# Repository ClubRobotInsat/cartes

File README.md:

# Cartes du club robot

Toutes les cartes ici sont les cartes en développement au club. Vous pouvez retrouver
dans les release les cartes correspondant à chaque robot.

Dans le dossier `manufactured` vous pouvez retrouver toutes les cartes qui ont été fabriquées. Elles sont
identifiées par un code unique que vous pouvez retrouver sur le PCB.

## Procédure de fabrication

Lorsque vous envoyez une carte à fabriquer, il faut:
- Ajouter un identifiant à la carte (de la forme `[A-Z]{3}`)
- Copier le projet dans le dossier `manufactured`
- Renommer le projet en `[identifiant] {nom}`

Cela permet d'avoir une trace exacte de toutes les cartes fabriquées. Une carte dans le dossier `manufactured` n'est pas
forcément définitive, mais cela permet d'identifier les cartes que nous pouvons trouver dans le local.

## Procédure post-coupe

Lorsque la coupe est finie il faut produire une release contenant toutes les cartes utilisées, c'est pratique pour comprendre
comment fonctionnait le robot.

## Cartes

### Alimentation

Carte principale d'alimentation du robot, adapte la tension batterie pour alimenter les différets composants.

### Base roulante

Carte pour la gestion de la base roulante du robot

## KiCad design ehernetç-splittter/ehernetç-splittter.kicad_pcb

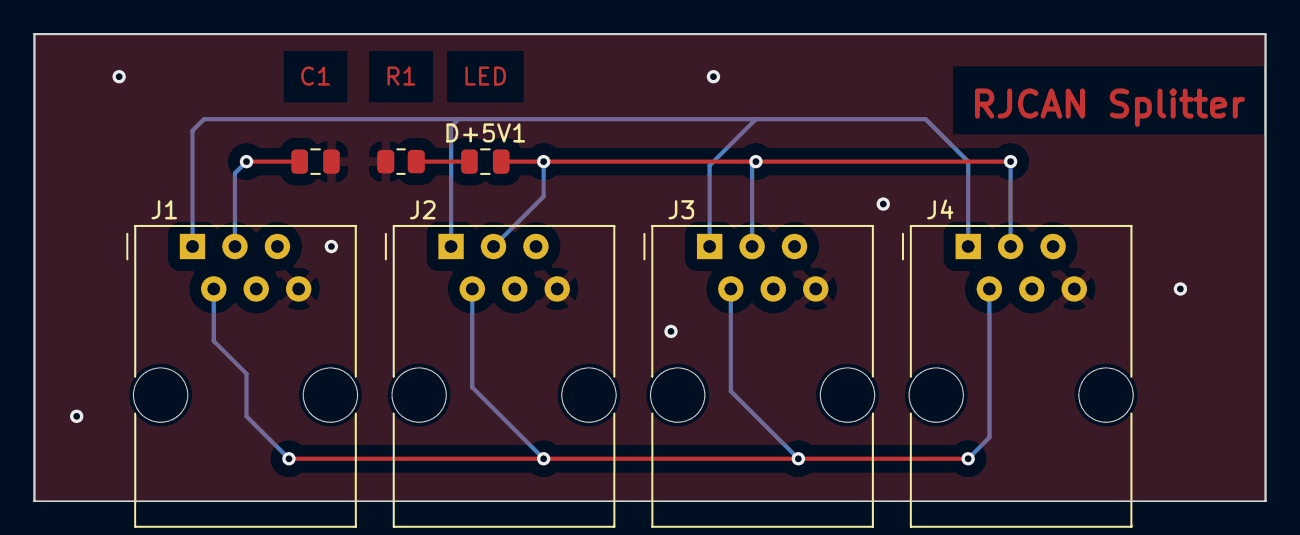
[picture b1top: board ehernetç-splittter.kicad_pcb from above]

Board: 2 copper layers, 73.7 x 27.9 mm, 7 parts (0 on the bottom side), 5 nets.

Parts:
C1: C_Polarized; C_0805_2012Metric
D+5V1: LED; C_0805_2012Metric
J1, J2, J3, J4: RJ_can; RJ12
R1: R; R_0805_2012Metric

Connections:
+5V: C1.1, D+5V1.2 (A), J1.3 (+5V), J2.3 (+5V), J3.3 (+5V), J4.3 (+5V)
CANH: J1.2 (CANH), J2.2 (CANH), J3.2 (CANH), J4.2 (CANH)
CANL: J1.1 (CANL), J2.1 (CANL), J3.1 (CANL), J4.1 (CANL)
GND: C1.2, J1.6 (GND), J2.6 (GND), J3.6 (GND), J4.6 (GND), R1.2
unnamed: D+5V1.1 (K), R1.1

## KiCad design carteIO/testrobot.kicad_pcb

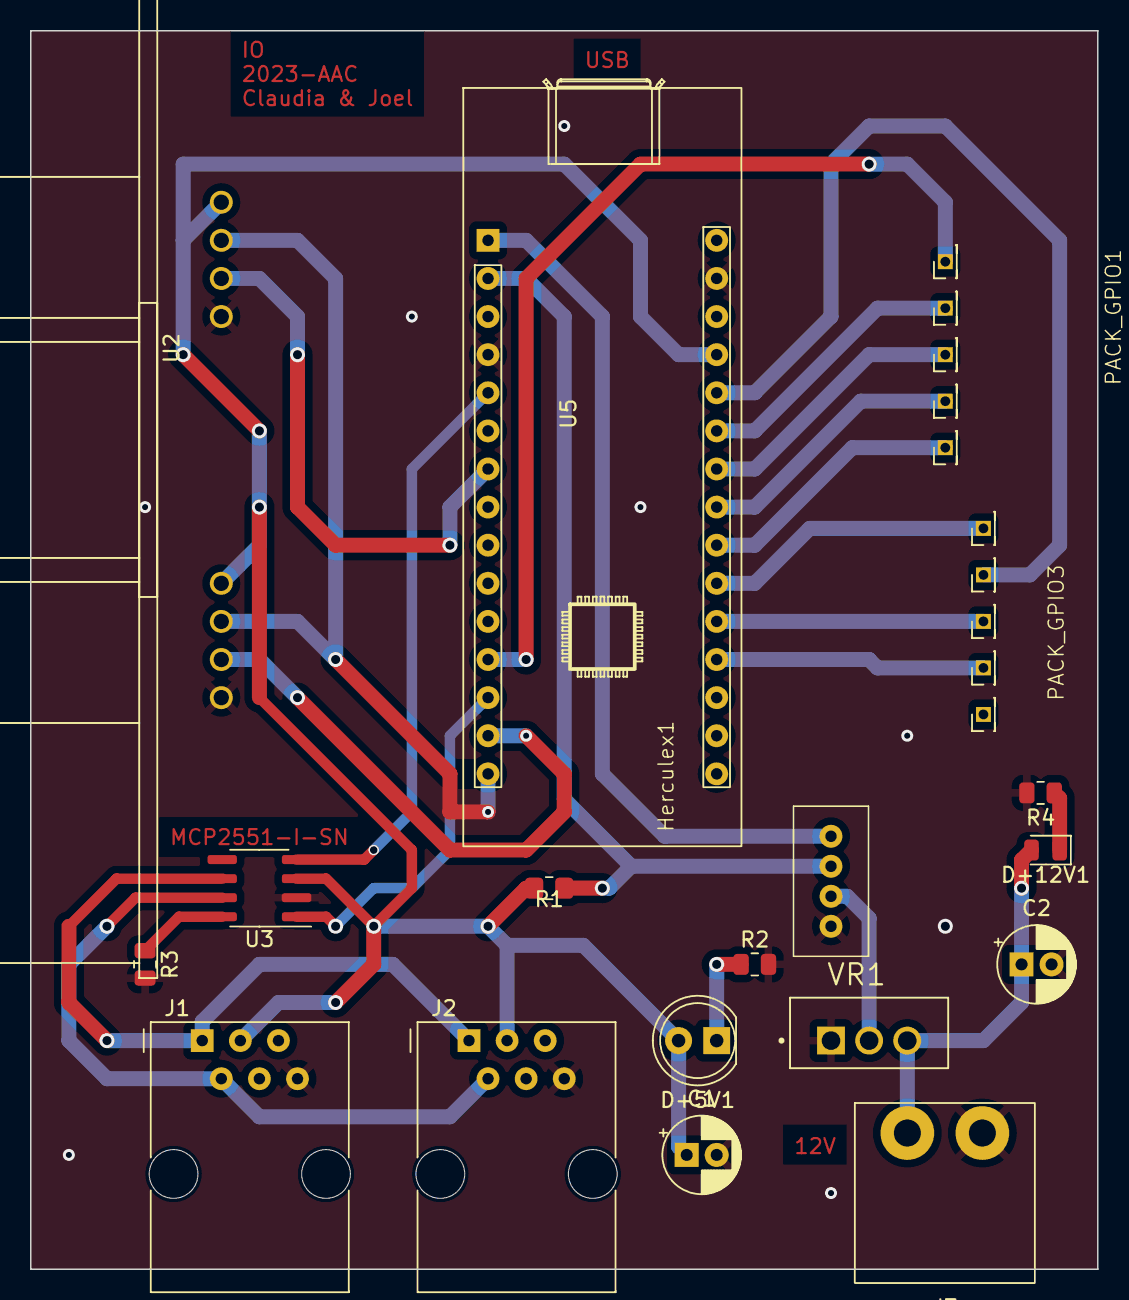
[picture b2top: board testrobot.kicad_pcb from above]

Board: 2 copper layers, 71.1 x 82.6 mm, 19 parts (0 on the bottom side), 26 nets.

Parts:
C1: C_Polarized; CP_Radial_D5.0mm_P2.00mm
C2: 470u; CP_Radial_D5.0mm_P2.00mm
D+5V1: LED; LED_D5.0mm
D+12V1: LED bleu; LED_0805_2012Metric
Herculex1: herculex
J1, J2: RJ_can; RJ12
J3: connector_power; WR_TBL_3137_2pins
PACK_GPIO1, PACK_GPIO3: gpio
R1: 4700; R_0805_2012Metric_Pad1.20x1.40mm_HandSolder
R2, R3: R; R_0805_2012Metric
R4: 1k; R_0805_2012Metric
U1, U2: HC-SR04; XCVR_HC-SR04
U3: MCP2551-I-SN; SOIC-8_3.9x4.9mm_P1.27mm
U5: Nucleo_STM32G431KB
VR1: LM317T/NOPB; TO254P1054X470X1955-3

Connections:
+5V: C1.1, D+5V1.2 (A), J1.3 (+5V), J2.3 (+5V), R1.1, U1.1 (VCC), U2.1 (VCC), U3.3 (VDD), U5.27 (+5V)
+8V: Herculex1.2 (+8V), VR1.2 (VOUT)
+12V: C2.1, D+12V1.2 (A), J3.1 (+12V), VR1.3 (VIN)
CANH: J1.2 (CANH), J2.2 (CANH), U3.7 (CANH)
CANL: J1.1 (CANL), J2.1 (CANL), U3.6 (CANL)
CAN_RX: U3.4 (RXD), U5.5 (PA12)
CAN_TX: U3.1 (TXD), U5.13 (PA11)
Echo_b5: U2.3 (ECHO), U5.14 (PB5)
Echo_b7: U1.3 (ECHO), U5.7 (PB7)
GND: C1.2, C2.2, Herculex1.1 (GND), J1.6 (GND), J2.6 (GND), J3.2 (GND), R2.2, R3.2, R4.2, U1.4 (GND), U2.4 (GND), U3.2 (VSS), U5.4 (GND), U5.29 (GND), VR1.1 (ADJ)
unnamed: D+5V1.1 (K), R2.1
unnamed: D+12V1.1 (K), R4.1
unnamed: R3.1, U3.8 (Rs)
unnamed: U5.3 (~RST), U5.28 (~RST)
PA0: PACK_GPIO3.2 (GPIO2), U5.19 (PA0)
PA1: PACK_GPIO3.3 (GPIO3), U5.20 (PA1)
PA2: PACK_GPIO3.4 (GPIO4), U5.26 (PA2)
PA3: PACK_GPIO3.5 (GPIO5), U5.21 (PA3)
PA4: PACK_GPIO1.1 (GPIO1), U5.22 (PA4)
PA5: PACK_GPIO1.2 (GPIO2), U5.23 (PA5/PB7)
PA6: PACK_GPIO1.3 (GPIO3), U5.24 (PA6/PA15)
PA7: PACK_GPIO1.4 (GPIO4), U5.25 (PA7)
PA8: PACK_GPIO1.5 (GPIO5), U5.12 (PA8)
RX_Hercu: Herculex1.4 (RX), U5.1 (PA9)
TX_Herculex: Herculex1.3 (TX), R1.2, U5.2 (PA10)
Trig_b4: U1.2 (TRIG), U2.2 (TRIG), U5.15 (PB4)

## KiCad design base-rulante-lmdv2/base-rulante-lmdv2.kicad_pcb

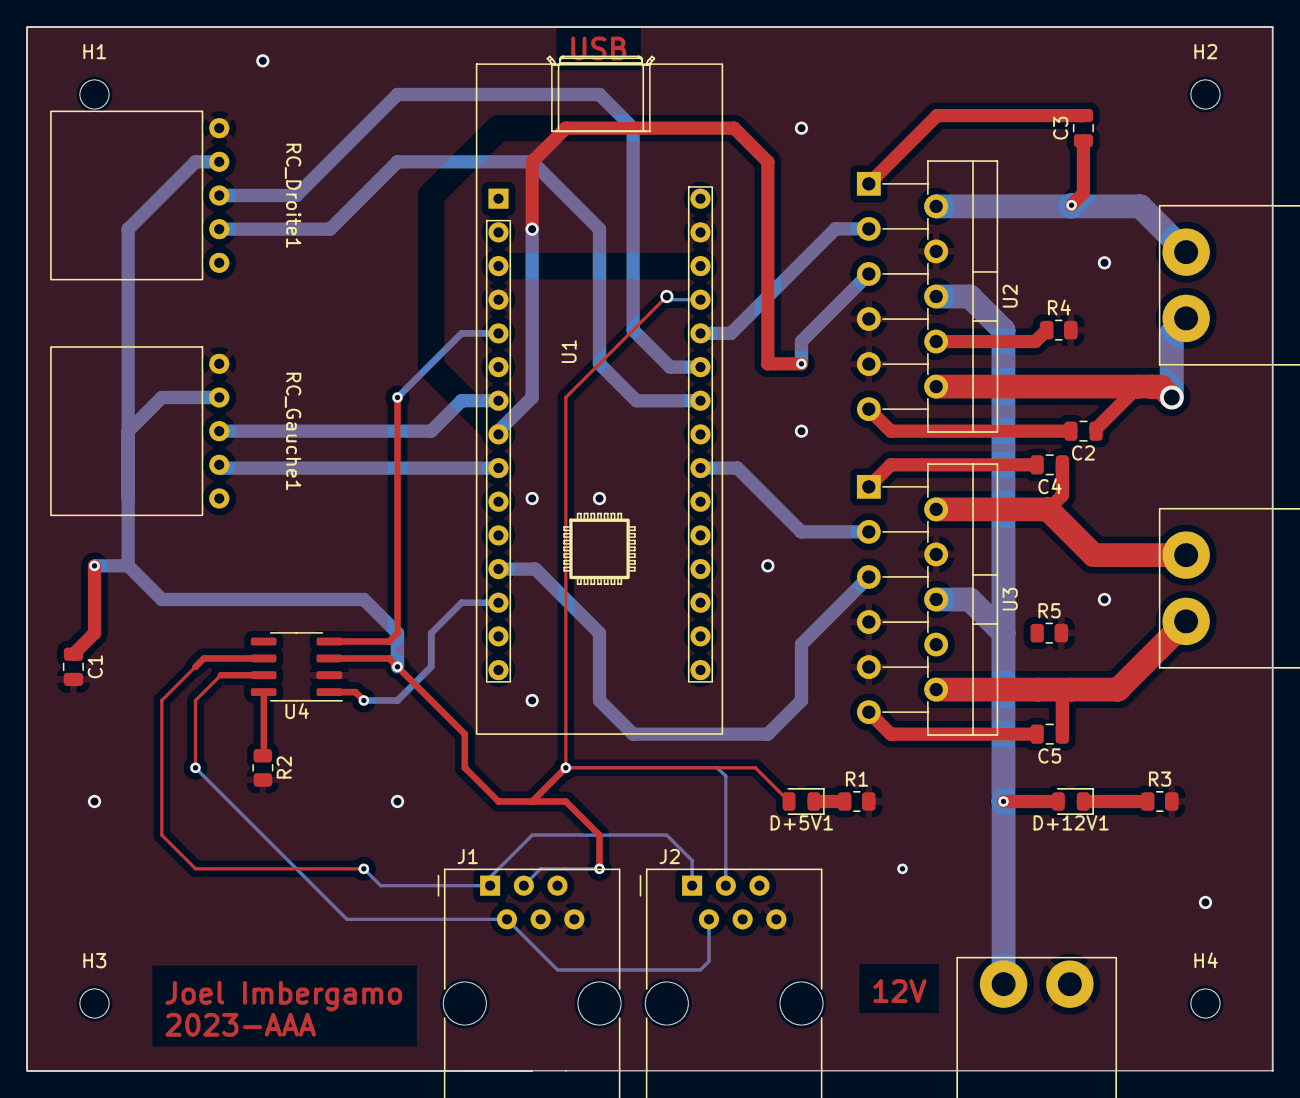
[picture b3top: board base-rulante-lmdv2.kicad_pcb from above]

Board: 2 copper layers, 94.0 x 78.7 mm, 27 parts (0 on the bottom side), 29 nets.

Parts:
C1, C2, C3, C4, C5: C_Polarized; C_0805_2012Metric
D+5V1, D+12V1: LED; LED_0805_2012Metric
H1, H2, H3, H4: MountingHole; MountingHole_2.2mm_M2
J1, J2: RJ_can; RJ12
J3, J4, J5: connector_power; WR_TBL_3137_2pins
R1, R2, R3, R4, R5: R; R_0805_2012Metric
RC_Droite1: roues_codeuses; HE14-5-angle
RC_Gauche1: roues_codeuses; HE14-5-angle
U1: Nucleo_STM32G431KB
U2, U3: LMD18200; TO-220-11_P3.4x5.08mm_StaggerOdd_Lead4.85mm_Vertical
U4: MCP2551-I-SN; SOIC-8_3.9x4.9mm_P1.27mm

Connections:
+5V: C1.1, D+5V1.2 (A), J1.3 (+5V), J2.3 (+5V), RC_Droite1.2 (+5V), RC_Gauche1.2 (+5V), U1.27 (+5V), U4.3 (VDD)
+12V: D+12V1.2 (A), J3.1 (+12V), U2.6 (VS), U3.6 (VS)
A_D: RC_Droite1.3 (A), U1.25 (PA7)
A_G: RC_Gauche1.3 (A), U1.7 (PB7)
B_D: RC_Droite1.4 (B), U1.24 (PA6/PA15)
B_G: RC_Gauche1.4 (B), U1.9 (PB6)
CANH: J1.2 (CANH), J2.2 (CANH), U4.7 (CANH)
CANL: J1.1 (CANL), J2.1 (CANL), U4.6 (CANL)
CAN_RX: U1.5 (PA12), U4.4 (RXD)
CAN_TX: U1.13 (PA11), U4.1 (TXD)
DIR_D: U1.26 (PA2), U2.3 (DIRECTION)
DIR_G: U1.22 (PA4), U3.3 (DIRECTION)
GND: C1.2, J1.6 (GND), J2.6 (GND), J3.2 (GND), R1.2, R2.2, R3.2, R4.2, R5.2, RC_Droite1.1 (GND), RC_Gauche1.1 (GND), U1.4 (GND), U1.29 (GND), U2.4 (BRAKE), U2.7 (GND), U2.9 (~THERMAL_FLAG_OUTPUT), U3.4 (BRAKE), U3.7 (GND), U3.9 (~THERMAL_FLAG_OUTPUT), U4.2 (VSS)
Mot_D_Out1: C3.1, J4.2 (GND), U2.2 (OUTPUT1)
Mot_D_Out2: C2.1, J4.1 (+12V), U2.10 (OUTPUT2)
Mot_G_Out1: C4.1, J5.2 (GND), U3.2 (OUTPUT1)
Mot_G_Out2: C5.1, J5.1 (+12V), U3.10 (OUTPUT2)
unnamed: D+5V1.1 (K), R1.1
unnamed: D+12V1.1 (K), R3.1
unnamed: U1.3 (~RST), U1.28 (~RST)
unnamed: C3.2, U2.1 (BOOTSTRAP1)
unnamed: C2.2, U2.11 (BOOTSTRAP2)
unnamed: R4.1, U2.8 (CURRENT_SENSE_OUTPUT)
unnamed: C4.2, U3.1 (BOOTSTRAP1)
unnamed: C5.2, U3.11 (BOOTSTRAP2)
unnamed: R5.1, U3.8 (CURRENT_SENSE_OUTPUT)
unnamed: R2.1, U4.8 (Rs)
PWM_D: U1.8 (PA15), U2.5 (PWM)
PWM_G: U1.12 (PA8), U3.5 (PWM)

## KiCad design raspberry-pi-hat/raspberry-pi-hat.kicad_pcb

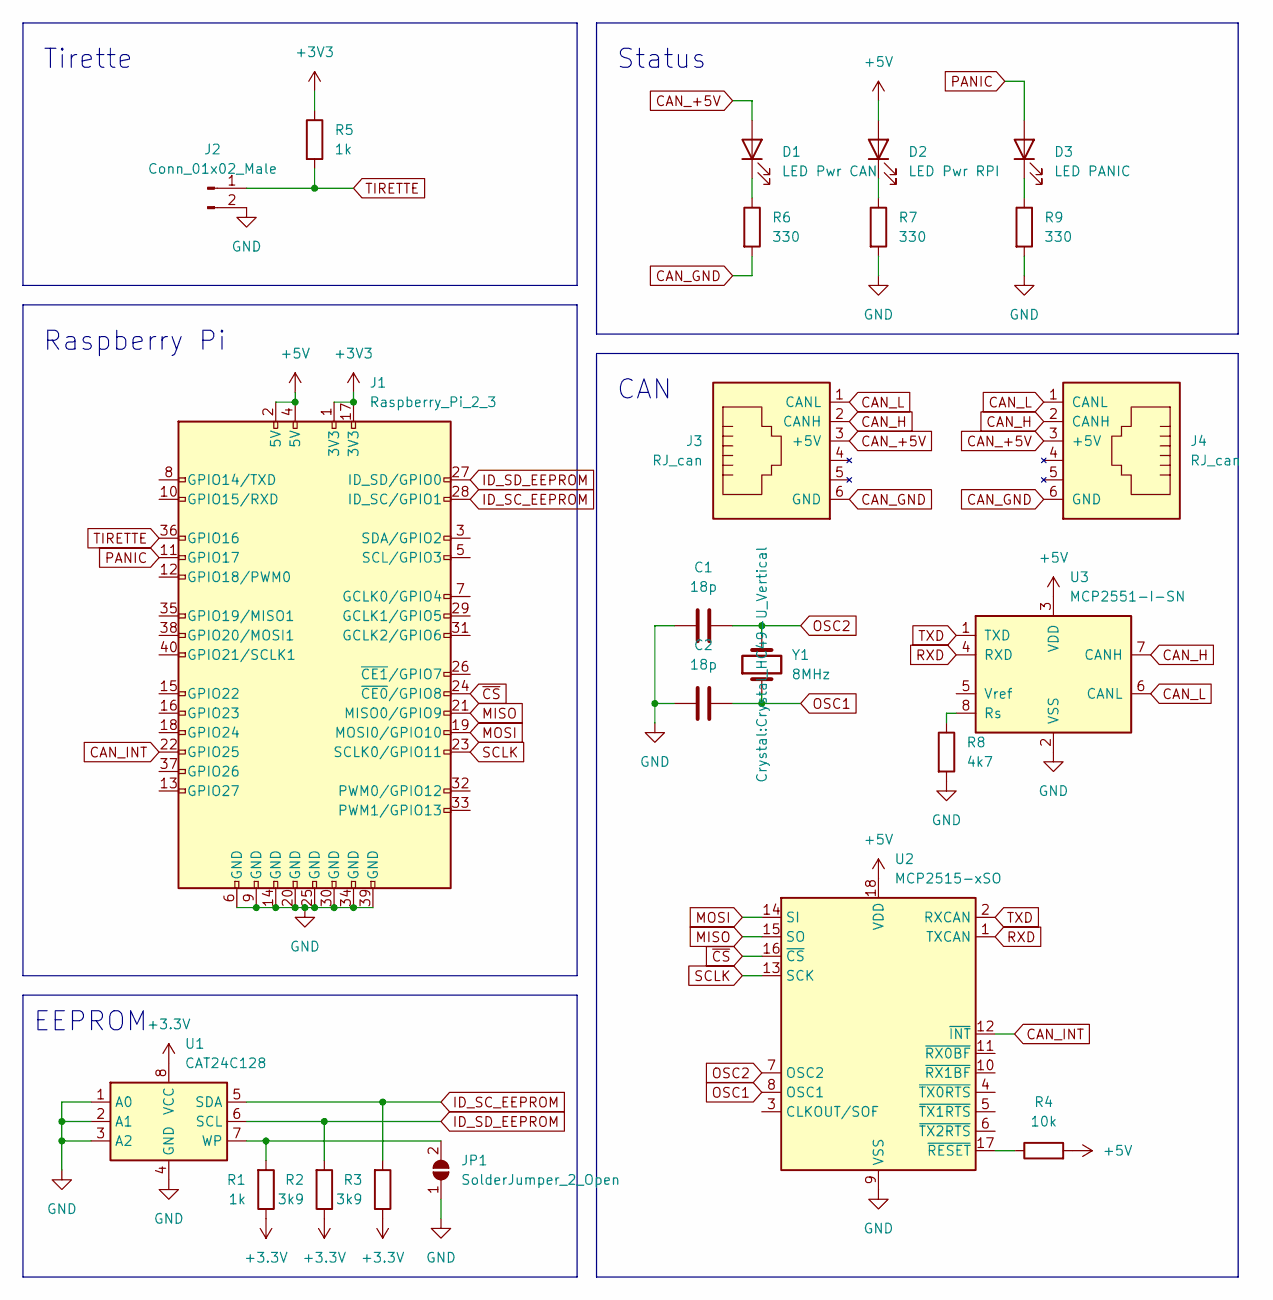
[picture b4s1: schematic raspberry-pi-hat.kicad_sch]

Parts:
C1, C2: 18p; C_0805_2012Metric
D1: LED Pwr CAN; LED_0805_2012Metric
D2: LED Pwr RPI; LED_0805_2012Metric
D3: LED PANIC; LED_0805_2012Metric
J1: Raspberry_Pi_2_3; PinHeader_2x20_P2.54mm_Vertical
J2: Conn_01x02_Male; PinHeader_1x02_P2.54mm_Horizontal
J3, J4: RJ_can; RJ12
JP1: SolderJumper_2_Open; SolderJumper-2_P1.3mm_Open_TrianglePad1.0x1.5mm
R1, R5: 1k; R_0805_2012Metric
R2, R3: 3k9; R_0805_2012Metric
R4: 10k; R_0805_2012Metric
R6, R7, R9: 330; R_0805_2012Metric
R8: 4k7; R_0805_2012Metric
U1: CAT24C128; SOIC-8_3.9x4.9mm_P1.27mm
U2: MCP2515-xSO; SOIC-18W_7.5x11.6mm_P1.27mm
U3: MCP2551-I-SN; SOIC-8_3.9x4.9mm_P1.27mm
Y1: 8MHz; Crystal_HC49-U_Vertical

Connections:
+3.3V: R1.1, R2.1, R3.1, U1.8 (VCC)
+3V3: J1.1 (3V3), J1.17 (3V3), R5.1
+5V: D2.2 (A), J1.2 (5V), J1.4 (5V), R4.2, U2.18 (VDD), U3.3 (VDD)
CAN_+5V: D1.2 (A), J3.3 (+5V), J4.3 (+5V)
CAN_GND: J3.6 (GND), J4.6 (GND), R6.2
CAN_H: J3.2 (CANH), J4.2 (CANH), U3.7 (CANH)
CAN_INT: J1.22 (GPIO25), U2.12 (~INT)
CAN_L: J3.1 (CANL), J4.1 (CANL), U3.6 (CANL)
GND: C1.2, C2.1, J1.6 (GND), J1.9 (GND), J1.14 (GND), J1.20 (GND), J1.25 (GND), J1.30 (GND), J1.34 (GND), J1.39 (GND), J2.2, JP1.1 (A), R7.2, R8.2, R9.2, U1.1 (A0), U1.2 (A1), U1.3 (A2), U1.4 (GND), U2.9 (VSS), U3.2 (VSS)
ID_SC_EEPROM: J1.28 (ID_SC/GPIO1), R3.2, U1.5 (SDA)
ID_SD_EEPROM: J1.27 (ID_SD/GPIO0), R2.2, U1.6 (SCL)
MISO: J1.21 (MISO0/GPIO9), U2.15 (SO)
MOSI: J1.19 (MOSI0/GPIO10), U2.14 (SI)
unnamed: D1.1 (K), R6.1
unnamed: D2.1 (K), R7.1
unnamed: D3.1 (K), R9.1
unnamed: JP1.2 (B), R1.2, U1.7 (WP)
unnamed: R4.1, U2.17 (~RESET)
unnamed: R8.1, U3.8 (Rs)
OSC1: C2.2, U2.8 (OSC1), Y1.1
OSC2: C1.1, U2.7 (OSC2), Y1.2
PANIC: D3.2 (A), J1.11 (GPIO17)
RXD: U2.1 (TXCAN), U3.4 (RXD)
SCLK: J1.23 (SCLK0/GPIO11), U2.13 (SCK)
TIRETTE: J1.36 (GPIO16), J2.1, R5.2
TXD: U2.2 (RXCAN), U3.1 (TXD)
~CS: J1.24 (~CE0/GPIO8), U2.16 (~CS)

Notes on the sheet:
Status
Raspberry Pi
EEPROM
Tirette
CAN

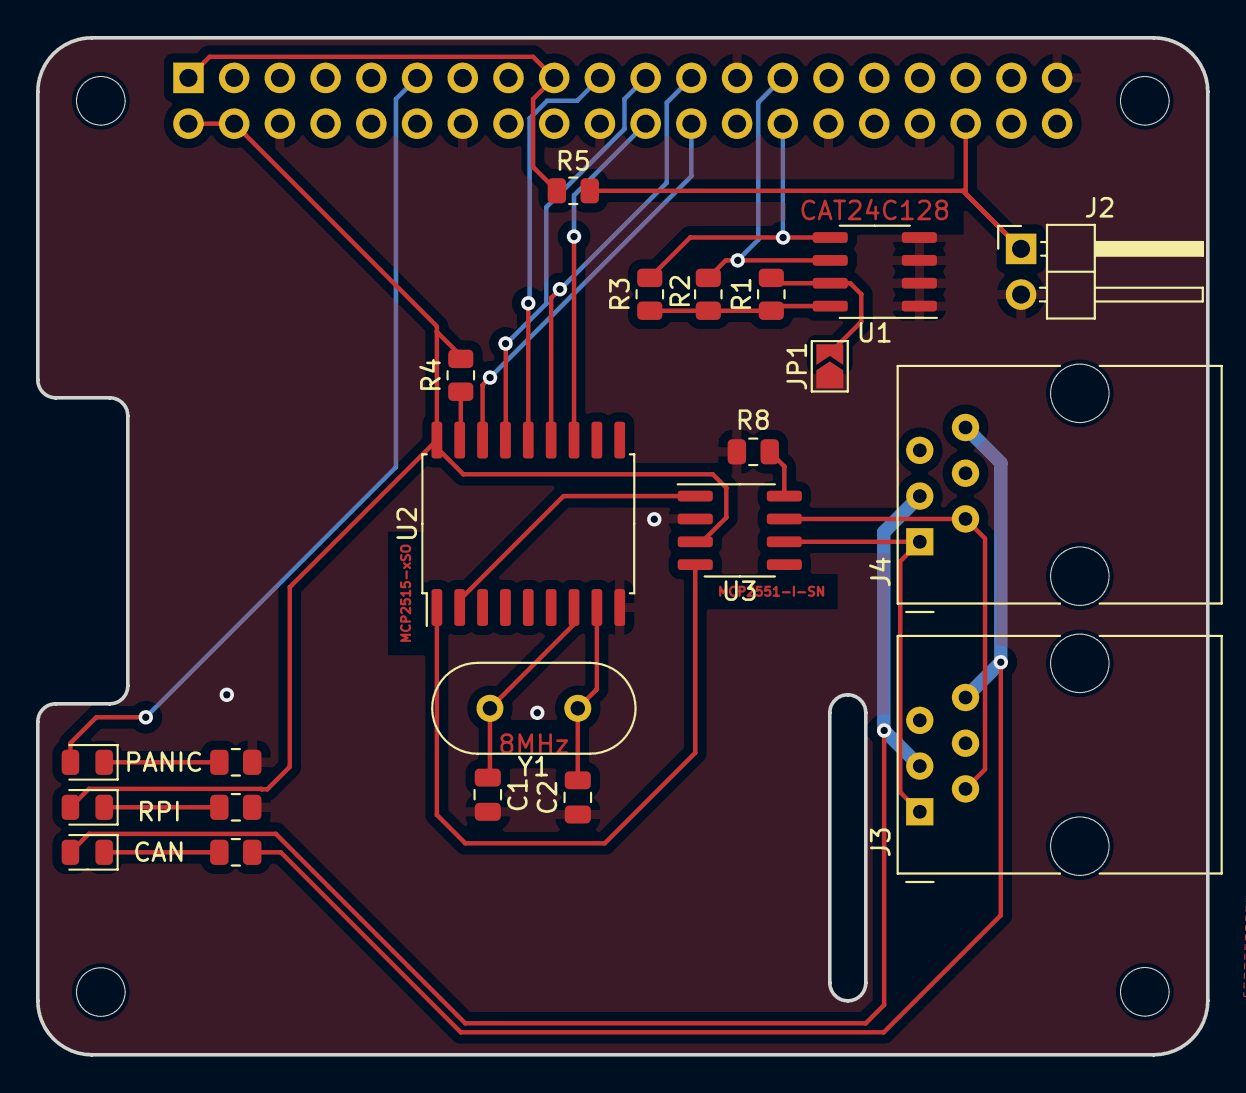
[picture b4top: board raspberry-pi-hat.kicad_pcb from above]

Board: 2 copper layers, 65.0 x 56.5 mm, 27 parts (1 on the bottom side), 27 nets.

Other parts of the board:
M1, M2, M3, M4: MountingHole_2.7mm

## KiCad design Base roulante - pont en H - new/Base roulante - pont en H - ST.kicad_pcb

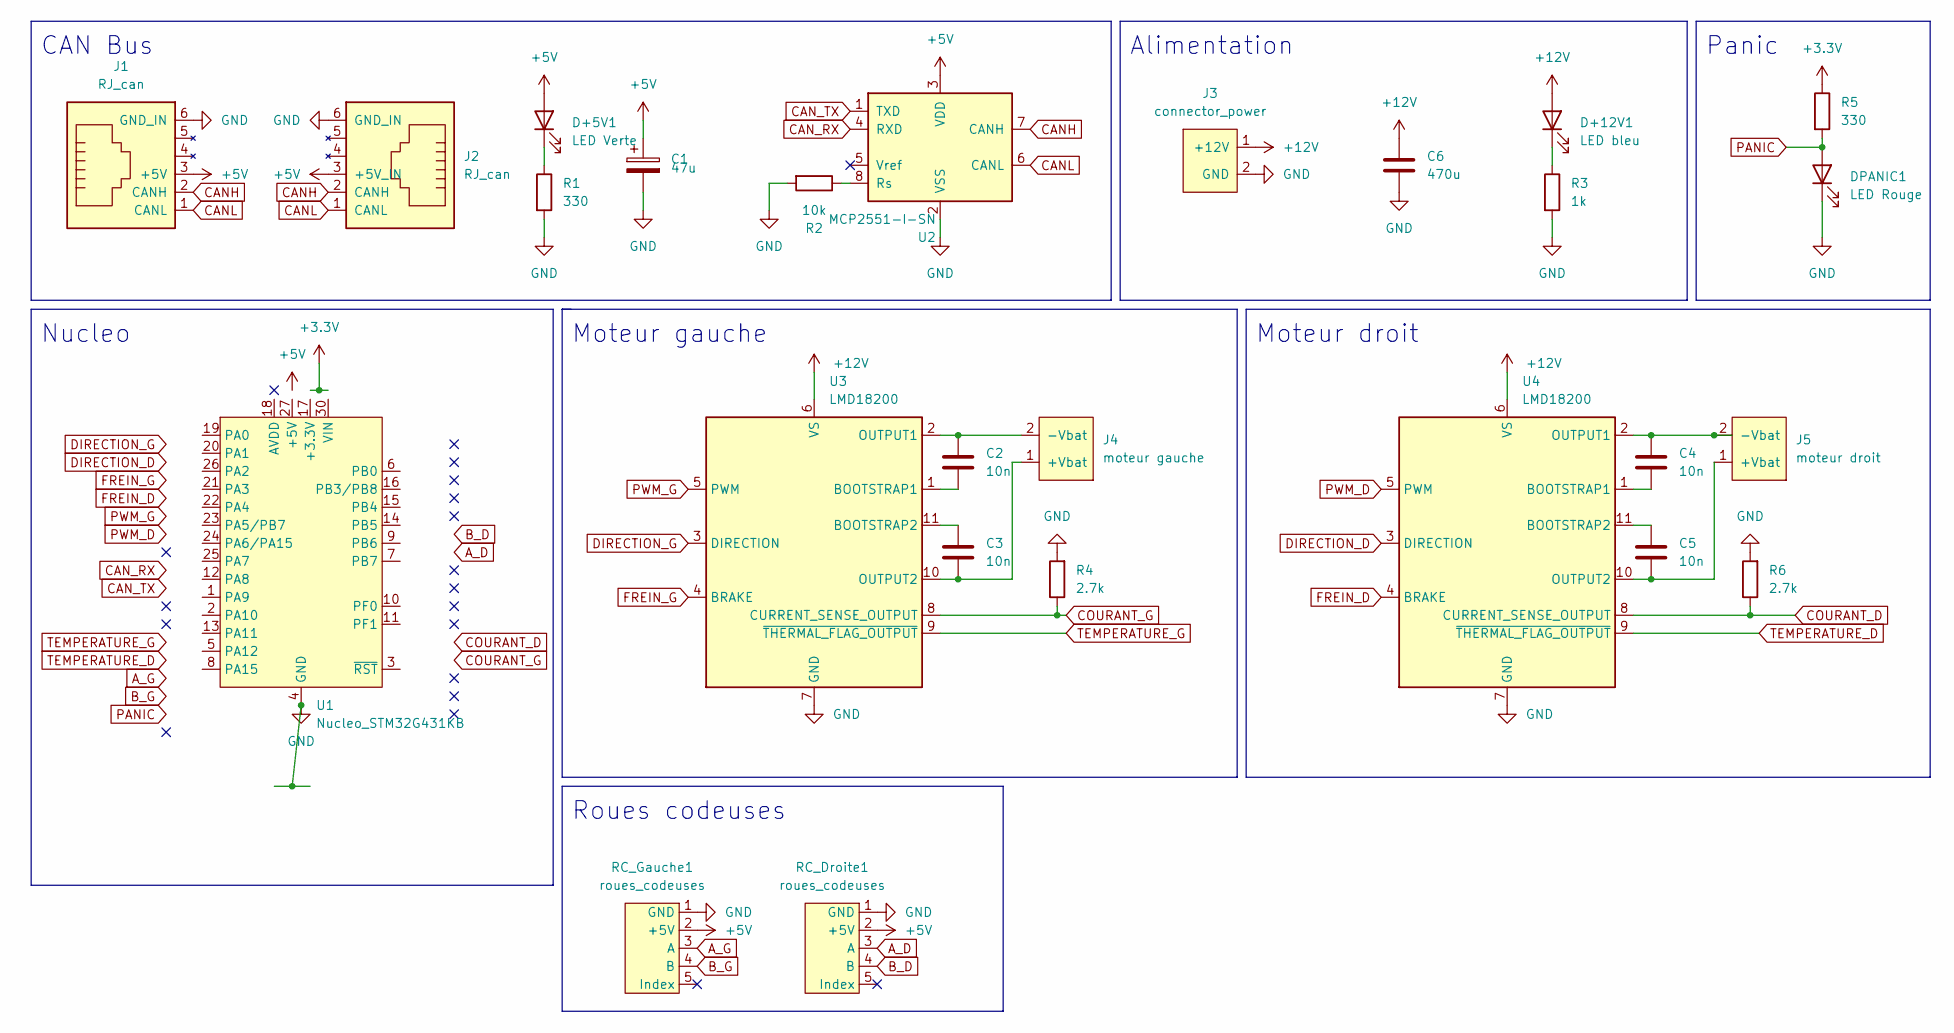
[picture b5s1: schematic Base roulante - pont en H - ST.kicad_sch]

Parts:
C1: 47u; CP_Radial_D5.0mm_P2.00mm
C2, C3, C4, C5: 10n; C_0805_2012Metric
C6: 470u; CP_Radial_D8.0mm_P3.50mm
D+5V1: LED Verte; LED_0805_2012Metric
D+12V1: LED bleu; LED_0805_2012Metric
DPANIC1: LED Rouge; LED_0805_2012Metric
J1, J2: RJ_can; RJ12
J3: connector_power; WR_TBL_3137_2pins
J4: moteur gauche; WR_TBL_3137_2pins
J5: moteur droit; WR_TBL_3137_2pins
R1, R5: 330; R_0805_2012Metric
R2: 10k; R_0805_2012Metric
R3: 1k; R_0805_2012Metric
R4, R6: 2.7k; R_0805_2012Metric
RC_Droite1: roues_codeuses; HE14-5-angle
RC_Gauche1: roues_codeuses; HE14-5-angle
U1: Nucleo_STM32G431KB
U2: MCP2551-I-SN; SOIC-8_3.9x4.9mm_P1.27mm
U3, U4: LMD18200; TO-220-11_P3.4x5.08mm_StaggerOdd_Lead4.85mm_Vertical

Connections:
+3.3V: R5.1
+5V: C1.1, D+5V1.2 (A), J1.3 (+5V), J2.3 (+5V_IN), RC_Droite1.2 (+5V), RC_Gauche1.2 (+5V), U2.3 (VDD)
+12V: C6.1, D+12V1.2 (A), J3.1 (+12V), U3.6 (VS), U4.6 (VS)
A_D: RC_Droite1.3 (A)
A_G: RC_Gauche1.3 (A)
B_D: RC_Droite1.4 (B)
B_G: RC_Gauche1.4 (B)
CANH: J1.2 (CANH), J2.2 (CANH), U2.7 (CANH)
CANL: J1.1 (CANL), J2.1 (CANL), U2.6 (CANL)
CAN_RX: U2.4 (RXD)
CAN_TX: U2.1 (TXD)
COURANT_D: R6.1, U4.8 (CURRENT_SENSE_OUTPUT)
COURANT_G: R4.1, U3.8 (CURRENT_SENSE_OUTPUT)
DIRECTION_D: U4.3 (DIRECTION)
DIRECTION_G: U3.3 (DIRECTION)
FREIN_D: U4.4 (BRAKE)
FREIN_G: U3.4 (BRAKE)
GND: C1.2, C6.2, DPANIC1.1 (K), J1.6 (GND_IN), J2.6 (GND_IN), J3.2 (GND), R1.2, R2.2, R3.2, R4.2, R6.2, RC_Droite1.1 (GND), RC_Gauche1.1 (GND), U1.4 (GND), U1.29 (GND), U2.2 (VSS), U3.7 (GND), U4.7 (GND)
unnamed: C2.1, J4.2 (-Vbat), U3.2 (OUTPUT1)
unnamed: C2.2, U3.1 (BOOTSTRAP1)
unnamed: C3.1, U3.11 (BOOTSTRAP2)
unnamed: C3.2, J4.1 (+Vbat), U3.10 (OUTPUT2)
unnamed: C4.1, J5.2 (-Vbat), U4.2 (OUTPUT1)
unnamed: C4.2, U4.1 (BOOTSTRAP1)
unnamed: C5.1, U4.11 (BOOTSTRAP2)
unnamed: C5.2, J5.1 (+Vbat), U4.10 (OUTPUT2)
unnamed: D+5V1.1 (K), R1.1
unnamed: D+12V1.1 (K), R3.1
unnamed: R2.1, U2.8 (Rs)
unnamed: U1.3 (~RST), U1.28 (~RST)
PANIC: DPANIC1.2 (A), R5.2
PWM_D: U4.5 (PWM)
PWM_G: U3.5 (PWM)
TEMPERATURE_D: U4.9 (~THERMAL_FLAG_OUTPUT)
TEMPERATURE_G: U3.9 (~THERMAL_FLAG_OUTPUT)

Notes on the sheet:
Panic
Alimentation
CAN Bus
Moteur droit
Roues codeuses
Moteur gauche
Nucleo

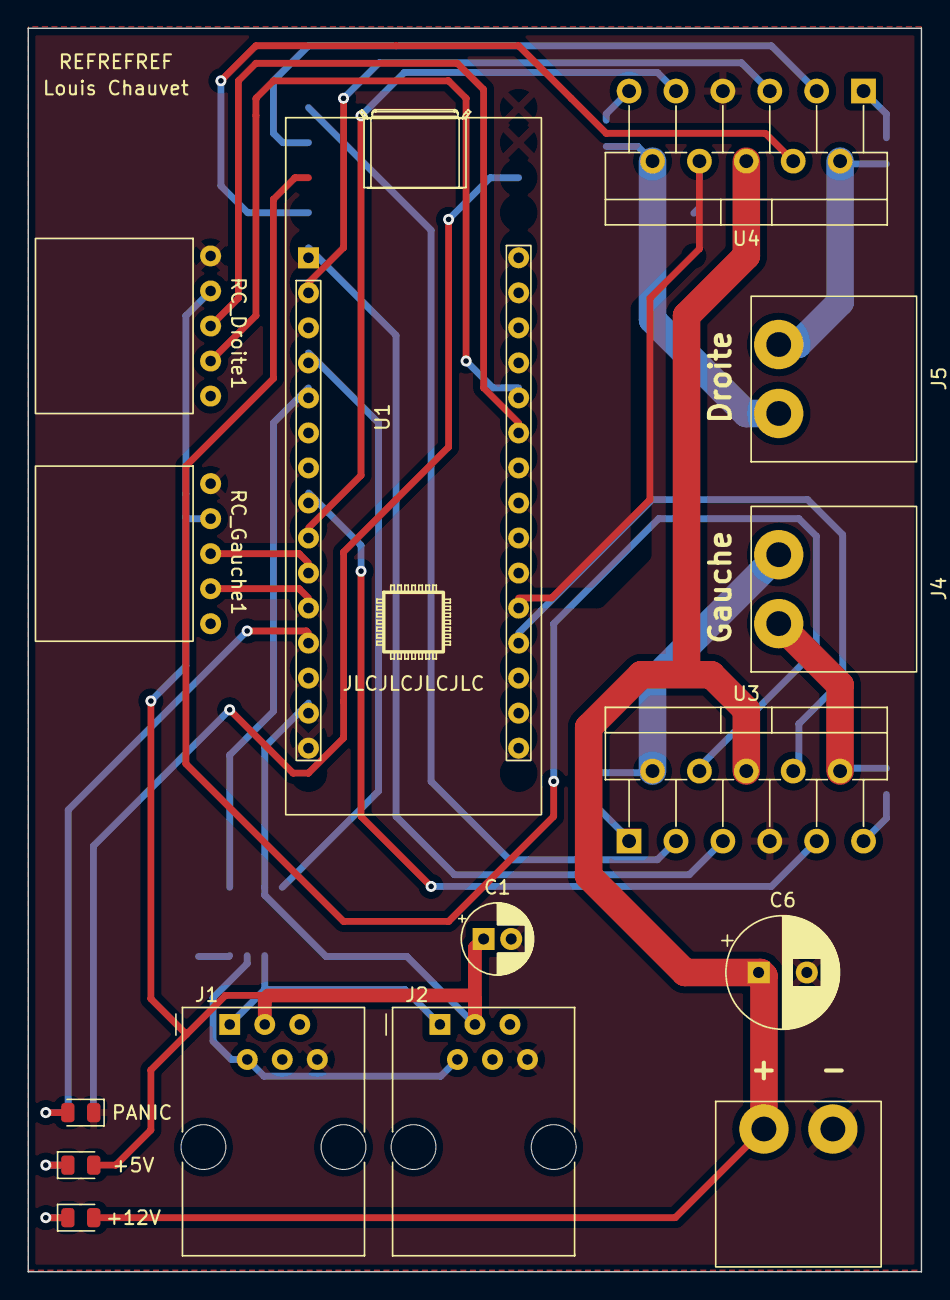
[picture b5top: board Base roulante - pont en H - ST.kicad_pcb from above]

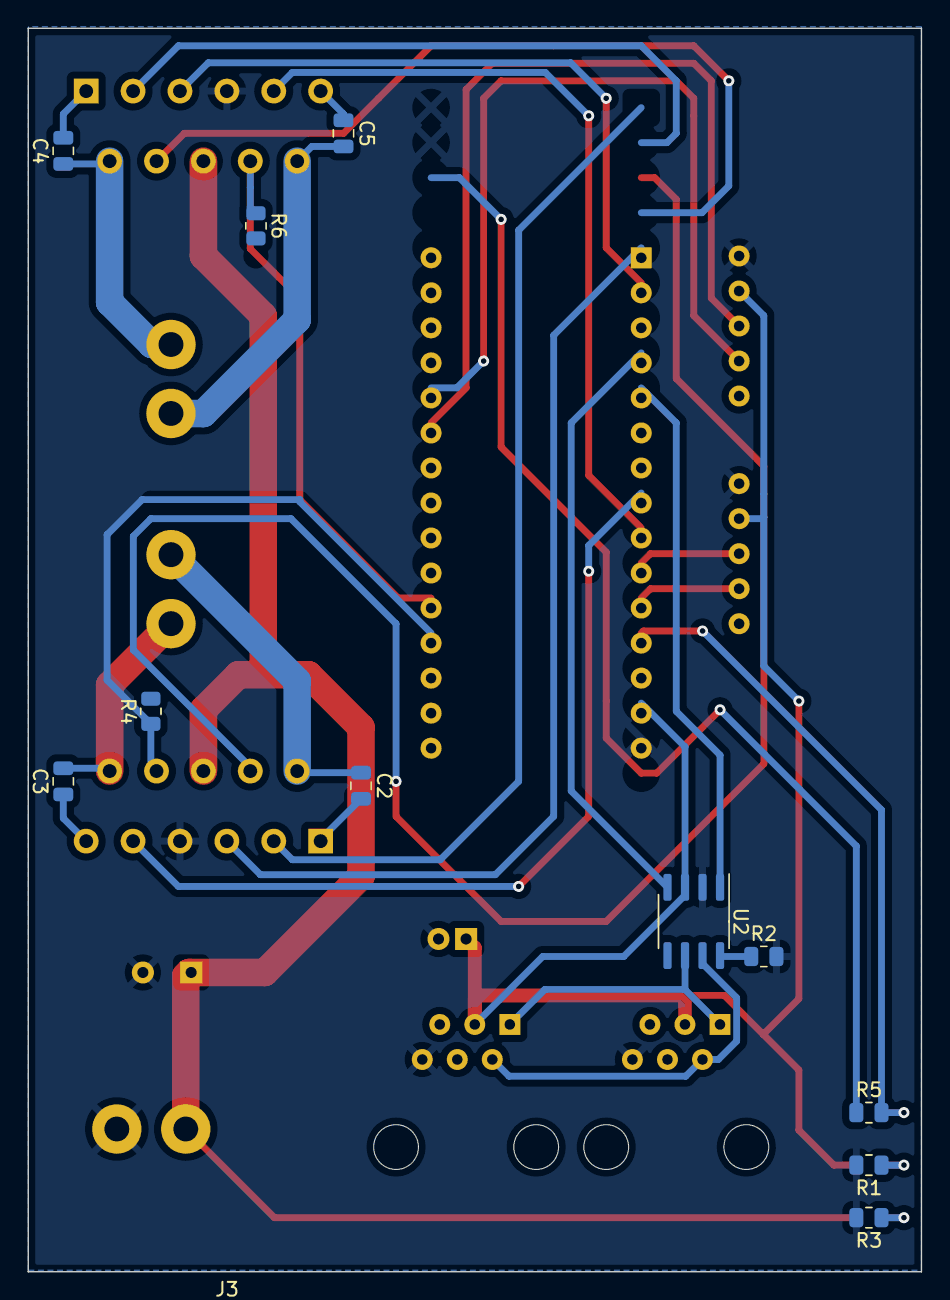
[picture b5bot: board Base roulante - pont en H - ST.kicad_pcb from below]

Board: 2 copper layers, 64.8 x 90.2 mm, 26 parts (11 on the bottom side), 20 nets.

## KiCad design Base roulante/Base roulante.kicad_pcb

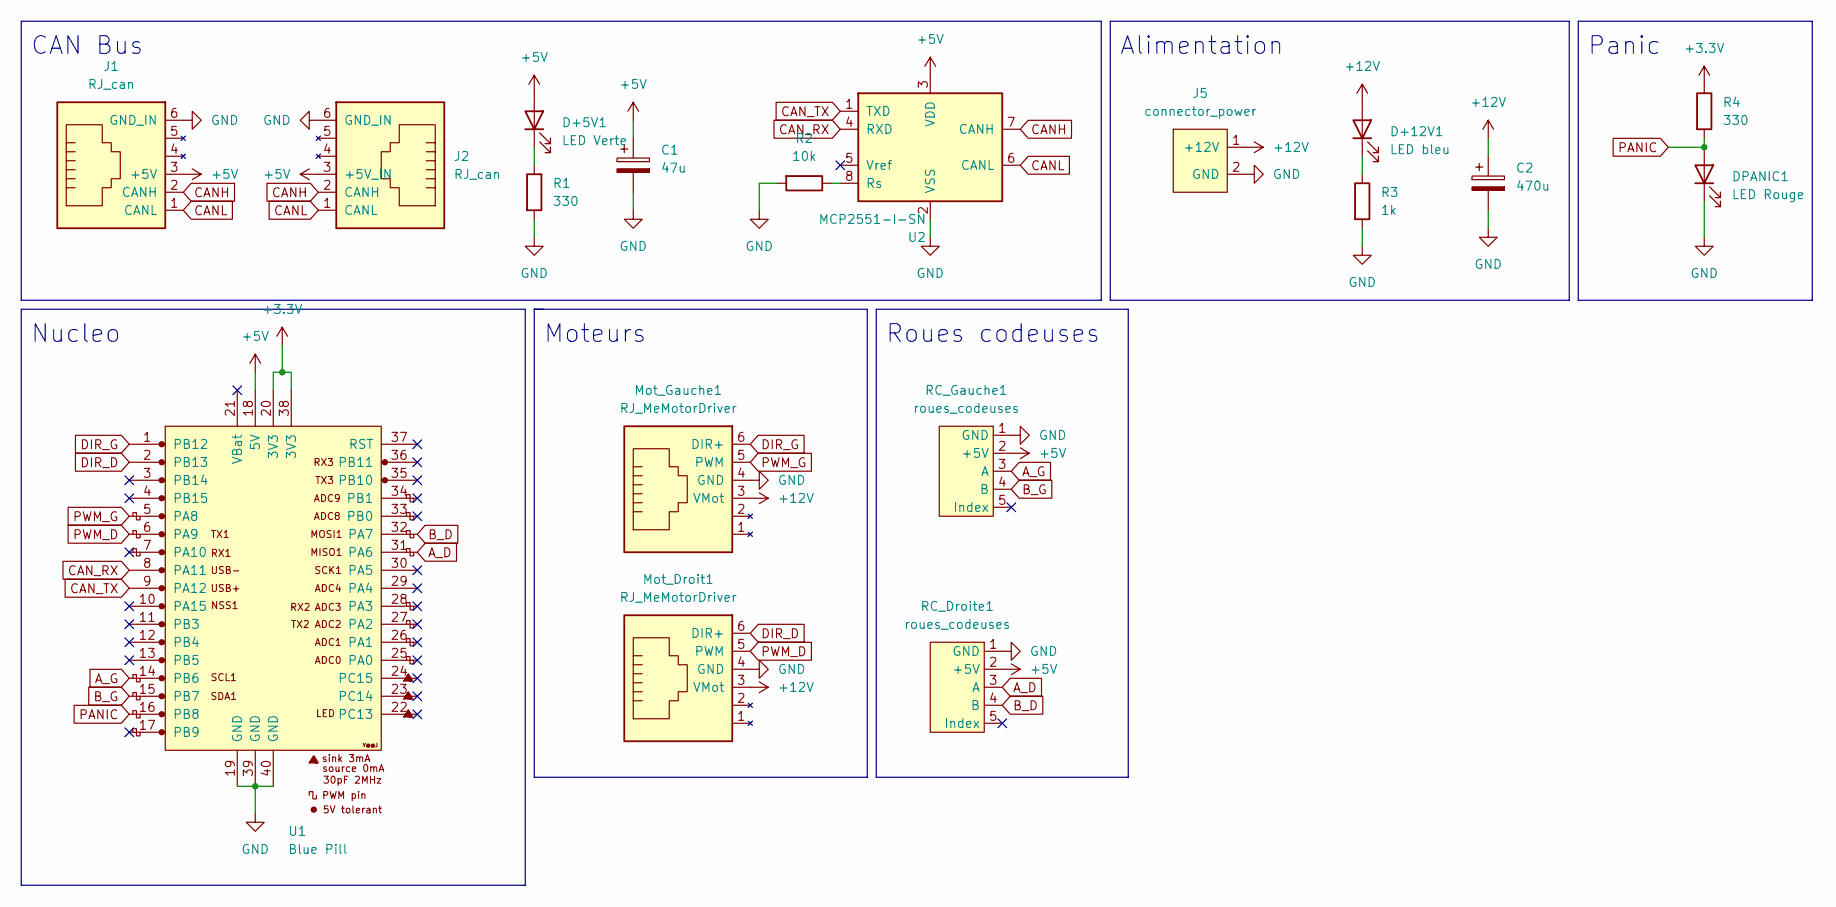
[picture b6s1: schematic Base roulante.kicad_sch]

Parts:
C1: 47u; CP_Radial_D5.0mm_P2.00mm
C2: 470u; CP_Radial_D5.0mm_P2.00mm
D+5V1: LED Verte; LED_0805_2012Metric
D+12V1: LED bleu; LED_0805_2012Metric
DPANIC1: LED Rouge; LED_0805_2012Metric
J1, J2: RJ_can; RJ12
J5: connector_power; WR_TBL_3137_2pins
Mot_Droit1: RJ_MeMotorDriver; RJ12
Mot_Gauche1: RJ_MeMotorDriver; RJ12
R1, R4: 330; R_0805_2012Metric
R2: 10k; R_0805_2012Metric
R3: 1k; R_0805_2012Metric
RC_Droite1: roues_codeuses; HE14-5-angle
RC_Gauche1: roues_codeuses; HE14-5-angle
U1: Blue Pill
U2: MCP2551-I-SN; SOIC-8_3.9x4.9mm_P1.27mm

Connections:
+3.3V: R4.1, U1.20 (3V3), U1.38 (3V3)
+5V: C1.1, D+5V1.2 (A), J1.3 (+5V), J2.3 (+5V_IN), RC_Droite1.2 (+5V), RC_Gauche1.2 (+5V), U1.18 (5V), U2.3 (VDD)
+12V: C2.1, D+12V1.2 (A), J5.1 (+12V), Mot_Droit1.3 (VMot), Mot_Gauche1.3 (VMot)
A_D: RC_Droite1.3 (A), U1.31 (PA6)
A_G: RC_Gauche1.3 (A), U1.14 (PB6)
B_D: RC_Droite1.4 (B), U1.32 (PA7)
B_G: RC_Gauche1.4 (B), U1.15 (PB7)
CANH: J1.2 (CANH), J2.2 (CANH), U2.7 (CANH)
CANL: J1.1 (CANL), J2.1 (CANL), U2.6 (CANL)
CAN_RX: U1.8 (PA11), U2.4 (RXD)
CAN_TX: U1.9 (PA12), U2.1 (TXD)
DIR_D: Mot_Droit1.6 (DIR+), U1.2 (PB13)
DIR_G: Mot_Gauche1.6 (DIR+), U1.1 (PB12)
GND: C1.2, C2.2, DPANIC1.1 (K), J1.6 (GND_IN), J2.6 (GND_IN), J5.2 (GND), Mot_Droit1.4 (GND), Mot_Gauche1.4 (GND), R1.2, R2.2, R3.2, RC_Droite1.1 (GND), RC_Gauche1.1 (GND), U1.19 (GND), U1.39 (GND), U1.40 (GND), U2.2 (VSS)
unnamed: D+5V1.1 (K), R1.1
unnamed: D+12V1.1 (K), R3.1
unnamed: R2.1, U2.8 (Rs)
PANIC: DPANIC1.2 (A), R4.2, U1.16 (PB8)
PWM_D: Mot_Droit1.5 (PWM), U1.6 (PA9)
PWM_G: Mot_Gauche1.5 (PWM), U1.5 (PA8)

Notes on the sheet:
Alimentation
Nucleo
CAN Bus
Roues codeuses
Panic
Moteurs

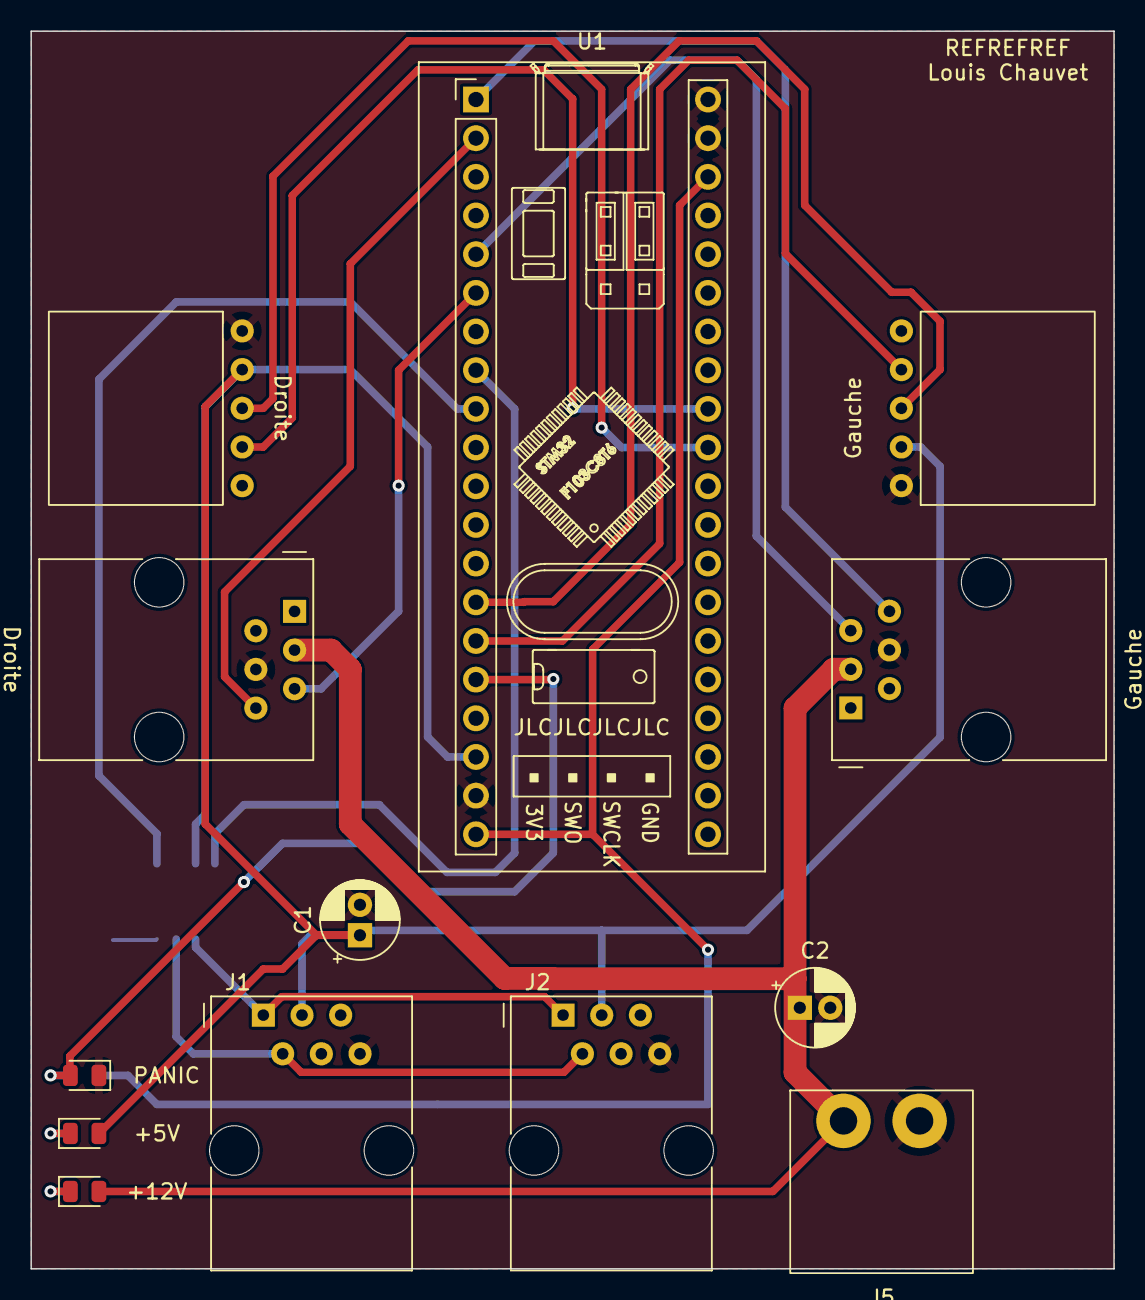
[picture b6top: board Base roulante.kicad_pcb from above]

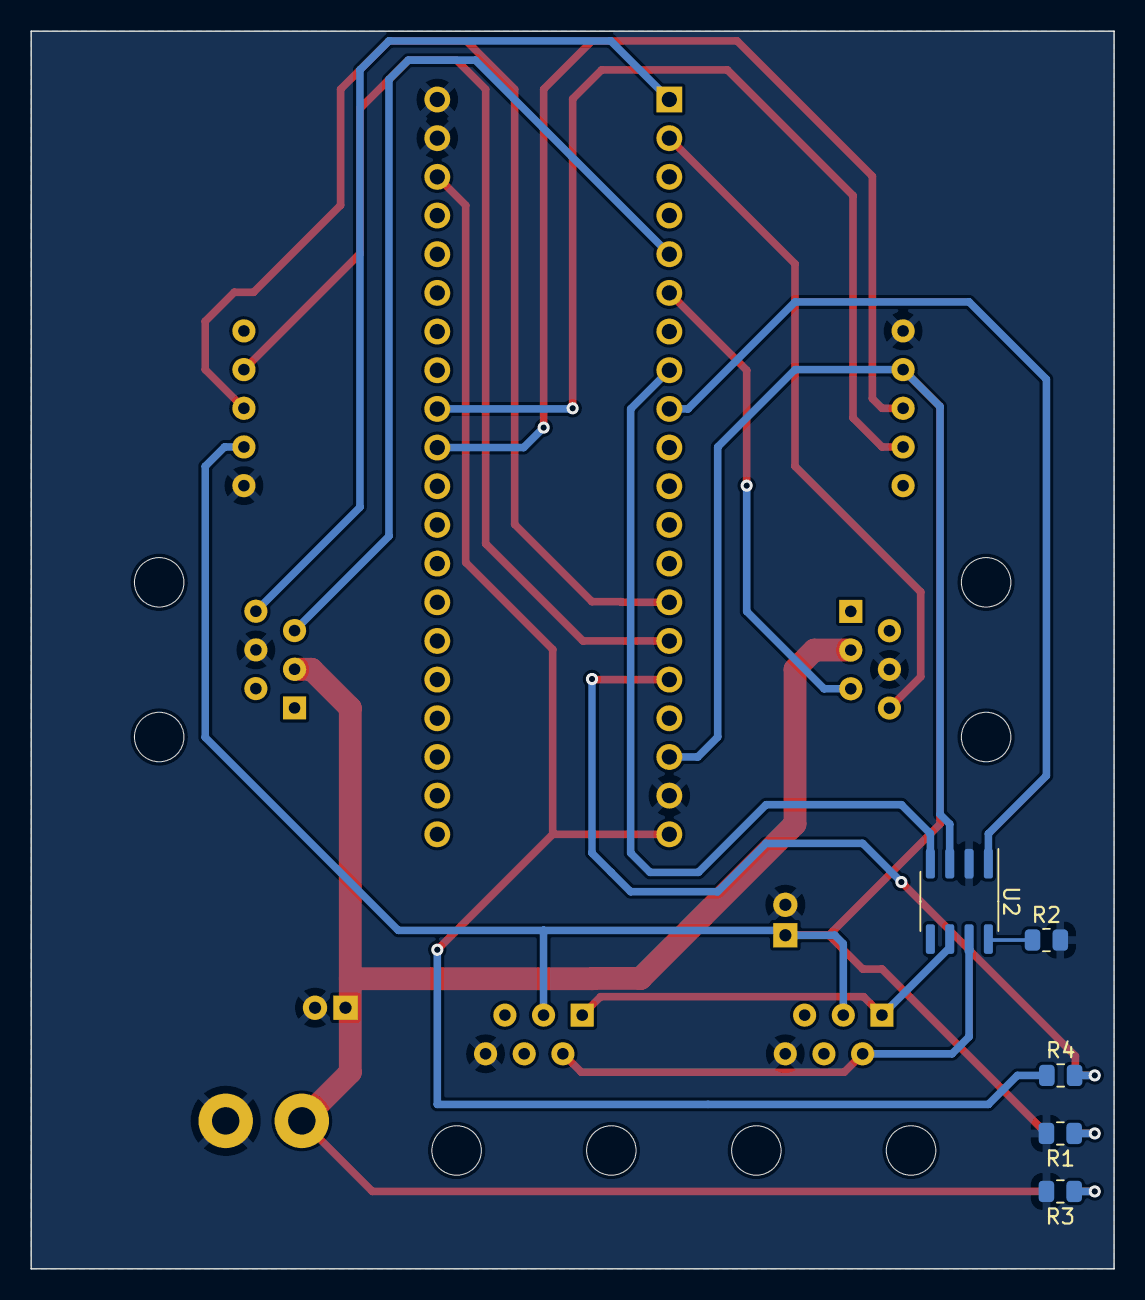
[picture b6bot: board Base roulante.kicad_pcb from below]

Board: 2 copper layers, 71.1 x 81.3 mm, 18 parts (5 on the bottom side), 20 nets.
